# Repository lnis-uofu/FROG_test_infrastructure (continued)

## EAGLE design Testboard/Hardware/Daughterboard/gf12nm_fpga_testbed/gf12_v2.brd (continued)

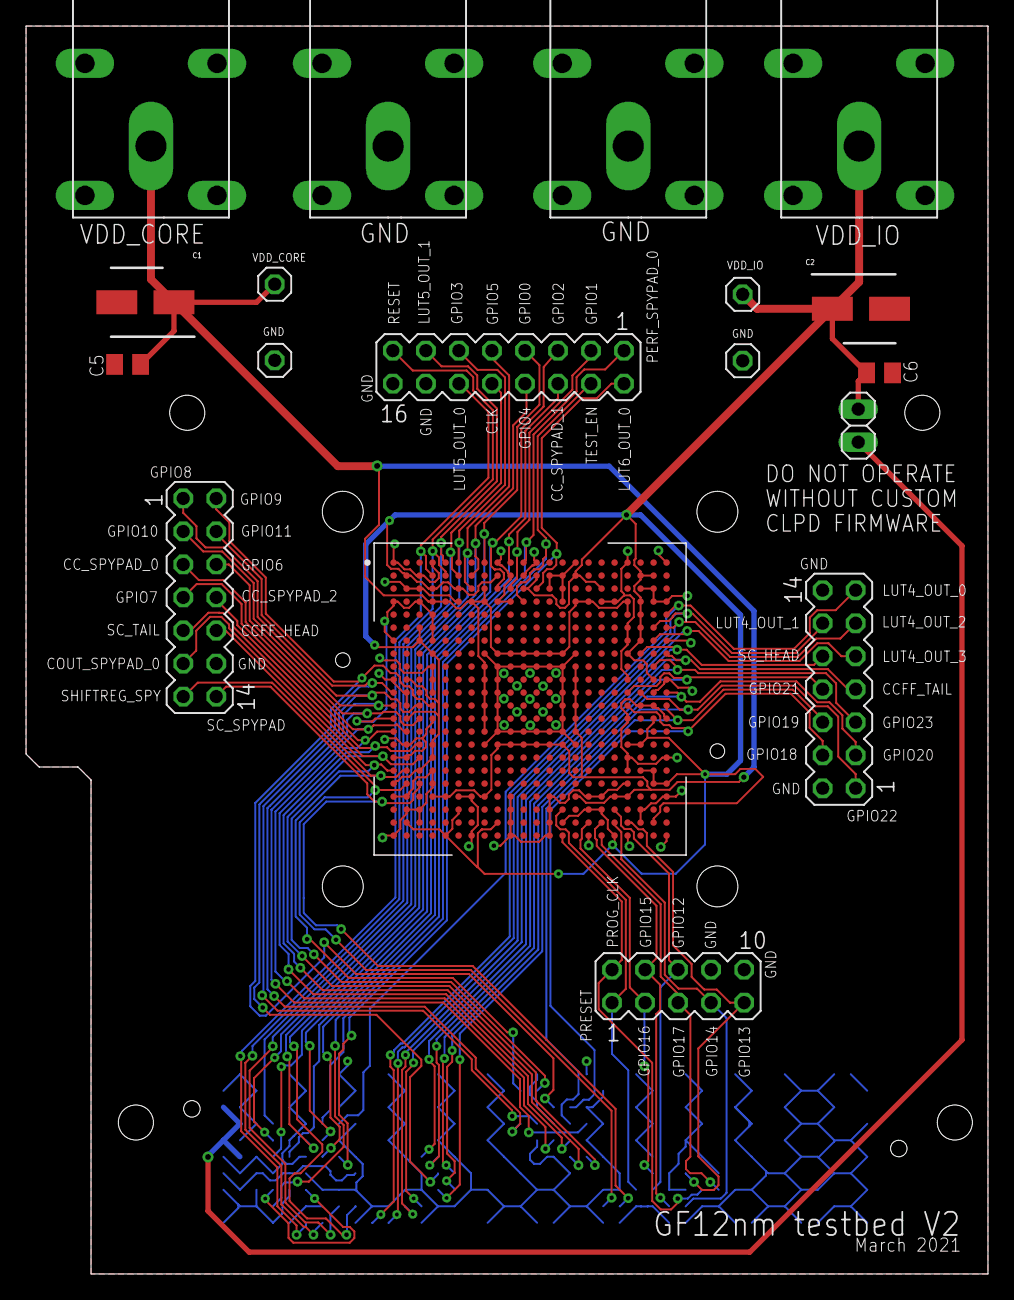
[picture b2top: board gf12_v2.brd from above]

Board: 2 copper layers, 74.0 x 96.0 mm, 19 parts (1 on the bottom side), 53 nets.

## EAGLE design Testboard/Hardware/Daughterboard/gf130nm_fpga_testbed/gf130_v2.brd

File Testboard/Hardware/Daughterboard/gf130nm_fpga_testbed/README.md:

# GF130nm PCB

## Pin Mappings

See [document](https://docs.google.com/spreadsheets/d/15zEyKyOejEvzYt_Ux2T2hlFm4bC0GtFkg6ObzwhrCUI) for pin mappings

## Changelog

### V2.2 Changes

**Critical Changes**
- Moved all pins connected to MPSoC MGT (bank 224) to other banks
- Moved all pins connected to lower-number TEBF0808 baord J1 pins to other banks
- Moved standoff mounting holes, were not lined up with TEBF0808 standoff holes

**Noncritical Changes**
- Extra FMC pins connected to more 2.54mm headers for MPSoC testbench GPIO
- Larger silkscreen text for 2.54mm headers

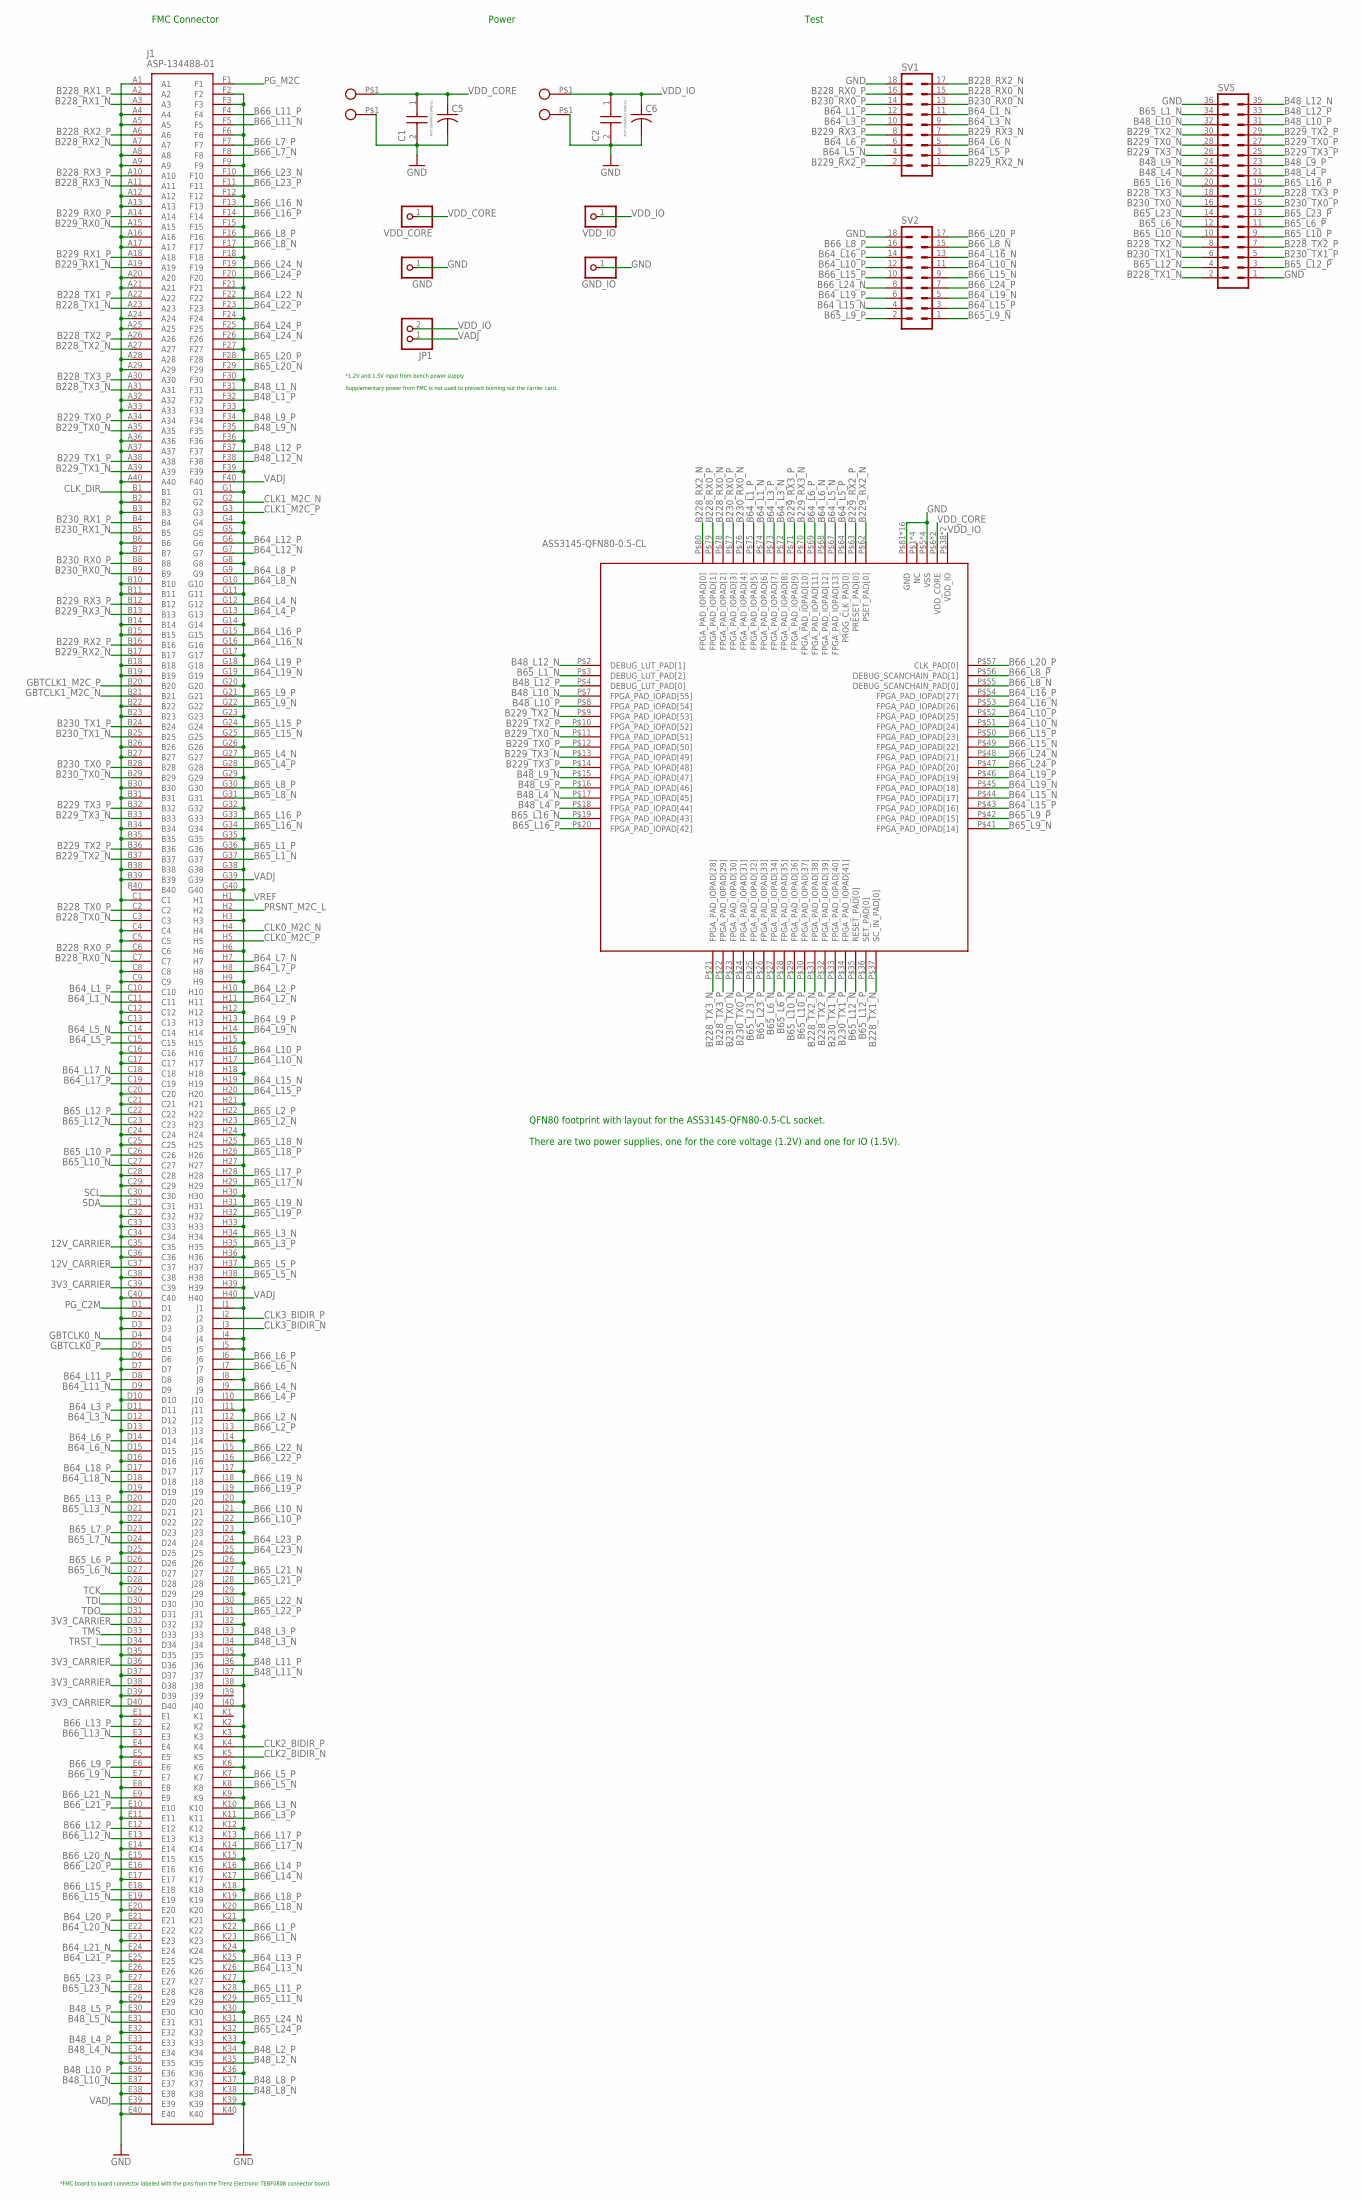
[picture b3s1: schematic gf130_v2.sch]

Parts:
C1, C2: APXT160ARA101ME61G; CAPAE530X610N
C5, C6: C-USC0805K; C0805K
GND: PINHD-1X1; 1X01
GND_IO: PINHD-1X1; 1X01
J1: ASP-134488-01; ASP13448801
JP1: PINHD-1X2; 1X02
SV1, SV2: MA09-2
SV5: MA18-2
U$2: QFN80; GF130
U$3, U$4, U$5: BANANA_JACK; 73099
VDD: BANANA_JACK; 73099
VDD_CORE: PINHD-1X1; 1X01
VDD_IO: PINHD-1X1; 1X01

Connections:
3V3_CARRIER: J1.C39, J1.D32, J1.D36, J1.D38, J1.D40
12V_CARRIER: J1.C35, J1.C37
B48_L1_N: J1.F31
B48_L1_P: J1.F32
B48_L2_N: J1.K35
B48_L2_P: J1.K34
B48_L3_N: J1.J34
B48_L3_P: J1.J33
B48_L4_N: J1.E34, SV5.22, U$2.P$17 (FPGA_PAD_IOPAD[45])
B48_L4_P: J1.E33, SV5.21, U$2.P$18 (FPGA_PAD_IOPAD[44])
B48_L5_N: J1.E31
B48_L5_P: J1.E30
B48_L8_N: J1.K38
B48_L8_P: J1.K37
B48_L9_N: J1.F35, SV5.24, U$2.P$15 (FPGA_PAD_IOPAD[47])
B48_L9_P: J1.F34, SV5.23, U$2.P$16 (FPGA_PAD_IOPAD[46])
B48_L10_N: J1.E37, SV5.32, U$2.P$7 (FPGA_PAD_IOPAD[55])
B48_L10_P: J1.E36, SV5.31, U$2.P$8 (FPGA_PAD_IOPAD[54])
B48_L11_N: J1.J37
B48_L11_P: J1.J36
B48_L12_N: J1.F38, SV5.35, U$2.P$2 (DEBUG_LUT_PAD[1])
B48_L12_P: J1.F37, SV5.33, U$2.P$4 (DEBUG_LUT_PAD[0])
B64_L1_N: J1.C11, SV1.11, U$2.P$74 (FPGA_PAD_IOPAD[6])
B64_L1_P: J1.C10, SV1.12, U$2.P$75 (FPGA_PAD_IOPAD[5])
B64_L2_N: J1.H11
B64_L2_P: J1.H10
B64_L3_N: J1.D12, SV1.9, U$2.P$72 (FPGA_PAD_IOPAD[8])
B64_L3_P: J1.D11, SV1.10, U$2.P$73 (FPGA_PAD_IOPAD[7])
B64_L4_N: J1.G12
B64_L4_P: J1.G13
B64_L5_N: J1.C14, SV1.4, U$2.P$67 (FPGA_PAD_IOPAD[13])
B64_L5_P: J1.C15, SV1.3, U$2.P$64 (PROG_CLK_PAD[0])
B64_L6_N: J1.D15, SV1.5, U$2.P$68 (FPGA_PAD_IOPAD[12])
B64_L6_P: J1.D14, SV1.6, U$2.P$69 (FPGA_PAD_IOPAD[11])
B64_L7_N: J1.H7
B64_L7_P: J1.H8
B64_L8_N: J1.G10
B64_L8_P: J1.G9
B64_L9_N: J1.H14
B64_L9_P: J1.H13
B64_L10_N: J1.H17, SV2.11, U$2.P$51 (FPGA_PAD_IOPAD[24])
B64_L10_P: J1.H16, SV2.12, U$2.P$52 (FPGA_PAD_IOPAD[25])
B64_L11_N: J1.D9
B64_L11_P: J1.D8
B64_L12_N: J1.G7
B64_L12_P: J1.G6
B64_L13_N: J1.K26
B64_L13_P: J1.K25
B64_L15_N: J1.H19, SV2.4, U$2.P$44 (FPGA_PAD_IOPAD[17])
B64_L15_P: J1.H20, SV2.3, U$2.P$43 (FPGA_PAD_IOPAD[16])
B64_L16_N: J1.G16, SV2.13, U$2.P$53 (FPGA_PAD_IOPAD[26])
B64_L16_P: J1.G15, SV2.14, U$2.P$54 (FPGA_PAD_IOPAD[27])
B64_L17_N: J1.C18
B64_L17_P: J1.C19
B64_L18_N: J1.D18
B64_L18_P: J1.D17
B64_L19_N: J1.G19, SV2.5, U$2.P$45 (FPGA_PAD_IOPAD[18])
B64_L19_P: J1.G18, SV2.6, U$2.P$46 (FPGA_PAD_IOPAD[19])
B64_L20_N: J1.E22
B64_L20_P: J1.E21
B64_L21_N: J1.E24
B64_L21_P: J1.E25
B64_L22_N: J1.F22
B64_L22_P: J1.F23
B64_L23_N: J1.J25
B64_L23_P: J1.J24
B64_L24_N: J1.F26
B64_L24_P: J1.F25
B65_L1_N: J1.G37, SV5.34, U$2.P$3 (DEBUG_LUT_PAD[2])
B65_L1_P: J1.G36
B65_L2_N: J1.H23
B65_L2_P: J1.H22
B65_L3_N: J1.H34
B65_L3_P: J1.H35
B65_L4_N: J1.G27
B65_L4_P: J1.G28
B65_L5_N: J1.H38
B65_L5_P: J1.H37
B65_L6_N: J1.D27, SV5.12, U$2.P$27 (FPGA_PAD_IOPAD[34])
B65_L6_P: J1.D26, SV5.11, U$2.P$28 (FPGA_PAD_IOPAD[35])
B65_L7_N: J1.D24
B65_L7_P: J1.D23
B65_L8_N: J1.G31
B65_L8_P: J1.G30
B65_L9_N: J1.G22, SV2.1, U$2.P$41 (FPGA_PAD_IOPAD[14])
B65_L9_P: J1.G21, SV2.2, U$2.P$42 (FPGA_PAD_IOPAD[15])
B65_L10_N: J1.C27, SV5.10, U$2.P$29 (FPGA_PAD_IOPAD[36])
B65_L10_P: J1.C26, SV5.9, U$2.P$30 (FPGA_PAD_IOPAD[37])
B65_L11_N: J1.K29
B65_L11_P: J1.K28
B65_L12_N: J1.C23, SV5.4, U$2.P$35 (RESET_PAD[0])
B65_L12_P: J1.C22, SV5.3, U$2.P$36 (SET_PAD[0])
B65_L13_N: J1.D21
B65_L13_P: J1.D20
B65_L15_N: J1.G25
B65_L15_P: J1.G24
B65_L16_N: J1.G34, SV5.20, U$2.P$19 (FPGA_PAD_IOPAD[43])
B65_L16_P: J1.G33, SV5.19, U$2.P$20 (FPGA_PAD_IOPAD[42])
B65_L17_N: J1.H29
B65_L17_P: J1.H28
B65_L18_N: J1.H25
B65_L18_P: J1.H26
B65_L19_N: J1.H31
B65_L19_P: J1.H32
B65_L20_N: J1.F29
B65_L20_P: J1.F28
B65_L21_N: J1.J27
B65_L21_P: J1.J28
B65_L22_N: J1.J30
B65_L22_P: J1.J31
B65_L23_N: J1.E28, SV5.14, U$2.P$25 (FPGA_PAD_IOPAD[32])
B65_L23_P: J1.E27, SV5.13, U$2.P$26 (FPGA_PAD_IOPAD[33])
B65_L24_N: J1.K31
B65_L24_P: J1.K32
B66_L1_N: J1.K23
B66_L1_P: J1.K22
B66_L2_N: J1.J12
B66_L2_P: J1.J13
B66_L3_N: J1.K10
B66_L3_P: J1.K11
B66_L4_N: J1.J9
B66_L4_P: J1.J10
B66_L5_N: J1.K8
B66_L5_P: J1.K7
B66_L6_N: J1.J7
B66_L6_P: J1.J6
B66_L7_N: J1.F8
B66_L7_P: J1.F7
B66_L8_N: J1.F17, SV2.15, U$2.P$55 (DEBUG_SCANCHAIN_PAD[0])
B66_L8_P: J1.F16, SV2.16, U$2.P$56 (DEBUG_SCANCHAIN_PAD[1])
B66_L9_N: J1.E7
B66_L9_P: J1.E6
B66_L10_N: J1.J21
B66_L10_P: J1.J22
B66_L11_N: J1.F5
B66_L11_P: J1.F4
B66_L12_N: J1.E13
B66_L12_P: J1.E12
B66_L13_N: J1.E3
B66_L13_P: J1.E2
B66_L14_N: J1.K17
B66_L14_P: J1.K16
B66_L15_N: J1.E19, SV2.9, U$2.P$49 (FPGA_PAD_IOPAD[22])
B66_L15_P: J1.E18, SV2.10, U$2.P$50 (FPGA_PAD_IOPAD[23])
B66_L16_N: J1.F13
B66_L16_P: J1.F14
B66_L17_N: J1.K14
B66_L17_P: J1.K13
B66_L18_N: J1.K20
B66_L18_P: J1.K19
B66_L19_N: J1.J18
B66_L19_P: J1.J19
B66_L20_N: J1.E15
B66_L20_P: J1.E16, SV2.17, U$2.P$57 (CLK_PAD[0])
B66_L21_N: J1.E9
B66_L21_P: J1.E10
B66_L22_N: J1.J15
B66_L22_P: J1.J16
B66_L23_N: J1.F10
B66_L23_P: J1.F11
B66_L24_N: J1.F19, SV2.8, U$2.P$48 (FPGA_PAD_IOPAD[21])
B66_L24_P: J1.F20, SV2.7, U$2.P$47 (FPGA_PAD_IOPAD[20])
B228_RX0_N: J1.C7, SV1.15, U$2.P$78 (FPGA_PAD_IOPAD[2])
B228_RX0_P: J1.C6, SV1.16, U$2.P$79 (FPGA_PAD_IOPAD[1])
B228_RX1_N: J1.A3
B228_RX1_P: J1.A2
B228_RX2_N: J1.A7, SV1.17, U$2.P$80 (FPGA_PAD_IOPAD[0])
B228_RX2_P: J1.A6
B228_RX3_N: J1.A11
B228_RX3_P: J1.A10
B228_TX0_N: J1.C3
B228_TX0_P: J1.C2
B228_TX1_N: J1.A23, SV5.2, U$2.P$37 (SC_IN_PAD[0])
B228_TX1_P: J1.A22
B228_TX2_N: J1.A27, SV5.8, U$2.P$31 (FPGA_PAD_IOPAD[38])
B228_TX2_P: J1.A26, SV5.7, U$2.P$32 (FPGA_PAD_IOPAD[39])
B228_TX3_N: J1.A31, SV5.18, U$2.P$21 (FPGA_PAD_IOPAD[28])
B228_TX3_P: J1.A30, SV5.17, U$2.P$22 (FPGA_PAD_IOPAD[29])
B229_RX0_N: J1.A15
B229_RX0_P: J1.A14
B229_RX1_N: J1.A19
B229_RX1_P: J1.A18
B229_RX2_N: J1.B17, SV1.1, U$2.P$62 (PSET_PAD[0])
B229_RX2_P: J1.B16, SV1.2, U$2.P$63 (PRESET_PAD[0])
B229_RX3_N: J1.B13, SV1.7, U$2.P$70 (FPGA_PAD_IOPAD[10])
B229_RX3_P: J1.B12, SV1.8, U$2.P$71 (FPGA_PAD_IOPAD[9])
B229_TX0_N: J1.A35, SV5.28, U$2.P$11 (FPGA_PAD_IOPAD[51])
B229_TX0_P: J1.A34, SV5.27, U$2.P$12 (FPGA_PAD_IOPAD[50])
B229_TX1_N: J1.A39
B229_TX1_P: J1.A38
B229_TX2_N: J1.B37, SV5.30, U$2.P$9 (FPGA_PAD_IOPAD[53])
B229_TX2_P: J1.B36, SV5.29, U$2.P$10 (FPGA_PAD_IOPAD[52])
B229_TX3_N: J1.B33, SV5.26, U$2.P$13 (FPGA_PAD_IOPAD[49])
B229_TX3_P: J1.B32, SV5.25, U$2.P$14 (FPGA_PAD_IOPAD[48])
B230_RX0_N: J1.B9, SV1.13, U$2.P$76 (FPGA_PAD_IOPAD[4])
B230_RX0_P: J1.B8, SV1.14, U$2.P$77 (FPGA_PAD_IOPAD[3])
B230_RX1_N: J1.B5
B230_RX1_P: J1.B4
B230_TX0_N: J1.B29, SV5.16, U$2.P$23 (FPGA_PAD_IOPAD[30])
B230_TX0_P: J1.B28, SV5.15, U$2.P$24 (FPGA_PAD_IOPAD[31])
B230_TX1_N: J1.B25, SV5.6, U$2.P$33 (FPGA_PAD_IOPAD[40])
B230_TX1_P: J1.B24, SV5.5, U$2.P$34 (FPGA_PAD_IOPAD[41])
CLK0_M2C_N: J1.H4
CLK0_M2C_P: J1.H5
CLK1_M2C_N: J1.G2
CLK1_M2C_P: J1.G3
CLK2_BIDIR_N: J1.K5
CLK2_BIDIR_P: J1.K4
CLK3_BIDIR_N: J1.J3
CLK3_BIDIR_P: J1.J2
CLK_DIR: J1.B1
GBTCLK0_N: J1.D4
GBTCLK0_P: J1.D5
GBTCLK1_M2C_N: J1.B21
GBTCLK1_M2C_P: J1.B20
GND: C1.2 (-), C2.2 (-), C5.2, C6.2, GND.1, GND_IO.1, J1.A1, J1.A4, J1.A5, J1.A8, J1.A9, J1.A12, J1.A13, J1.A16, J1.A17, J1.A20, J1.A21, J1.A24, J1.A25, J1.A28, J1.A29, J1.A32, J1.A33, J1.A36, J1.A37, J1.A40, J1.B2, J1.B3, J1.B6, J1.B7, J1.B10, J1.B11, J1.B14, J1.B15, J1.B18, J1.B19, J1.B22, J1.B23, J1.B26, J1.B27, J1.B30, J1.B31, J1.B34, J1.B35, J1.B38, J1.B39, J1.C1, J1.C4, J1.C5, J1.C8, J1.C9, J1.C12, J1.C13, J1.C16, J1.C17, J1.C20, J1.C21, J1.C24, J1.C25, J1.C28, J1.C29, J1.C32, J1.C33, J1.C34, J1.C36, J1.C38, J1.C40, J1.D2, J1.D3, J1.D6, J1.D7, J1.D10, J1.D13, J1.D16, J1.D19, J1.D22, J1.D25, J1.D28, J1.D35, J1.D37, J1.D39, J1.E1, J1.E4, J1.E5, J1.E8, J1.E11, J1.E14, J1.E17, J1.E20, J1.E23, J1.E26, J1.E29, J1.E32, J1.E35, J1.E38, J1.E40, J1.F2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
PG_C2M: J1.D1
PG_M2C: J1.F1
PRSNT_M2C_L: J1.H2
SCL: J1.C30
SDA: J1.C31
TCK: J1.D29
TDI: J1.D30
TDO: J1.D31
TMS: J1.D33
TRST_L: J1.D34
VADJ: J1.E39, J1.F40, J1.G39, J1.H40, JP1.1
VDD_CORE: C1.1 (+), C5.1, U$2.P$6 (VDD_CORE), U$2.P$58 (VDD_CORE), VDD.P$1 (1), VDD_CORE.1
VDD_IO: C2.1 (+), C6.1, JP1.2, U$2.P$38 (VDD_IO), U$2.P$66 (VDD_IO), U$4.P$1 (1), VDD_IO.1
VREF: J1.H1

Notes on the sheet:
Power
FMC Connector
*1.2V and 1.5V input from bench power supply Supplementary power from FMC is not used to prevent burning out the carrier card.
*FMC board to board connector labeled with the pins from the Trenz Electronic TEBF0808 connector board.
QFN80 footprint with layout for the ASS3145-QFN80-0.5-CL socket. There are two power supplies, one for the core voltage (1.2V) and one for IO (1.5V).
Test

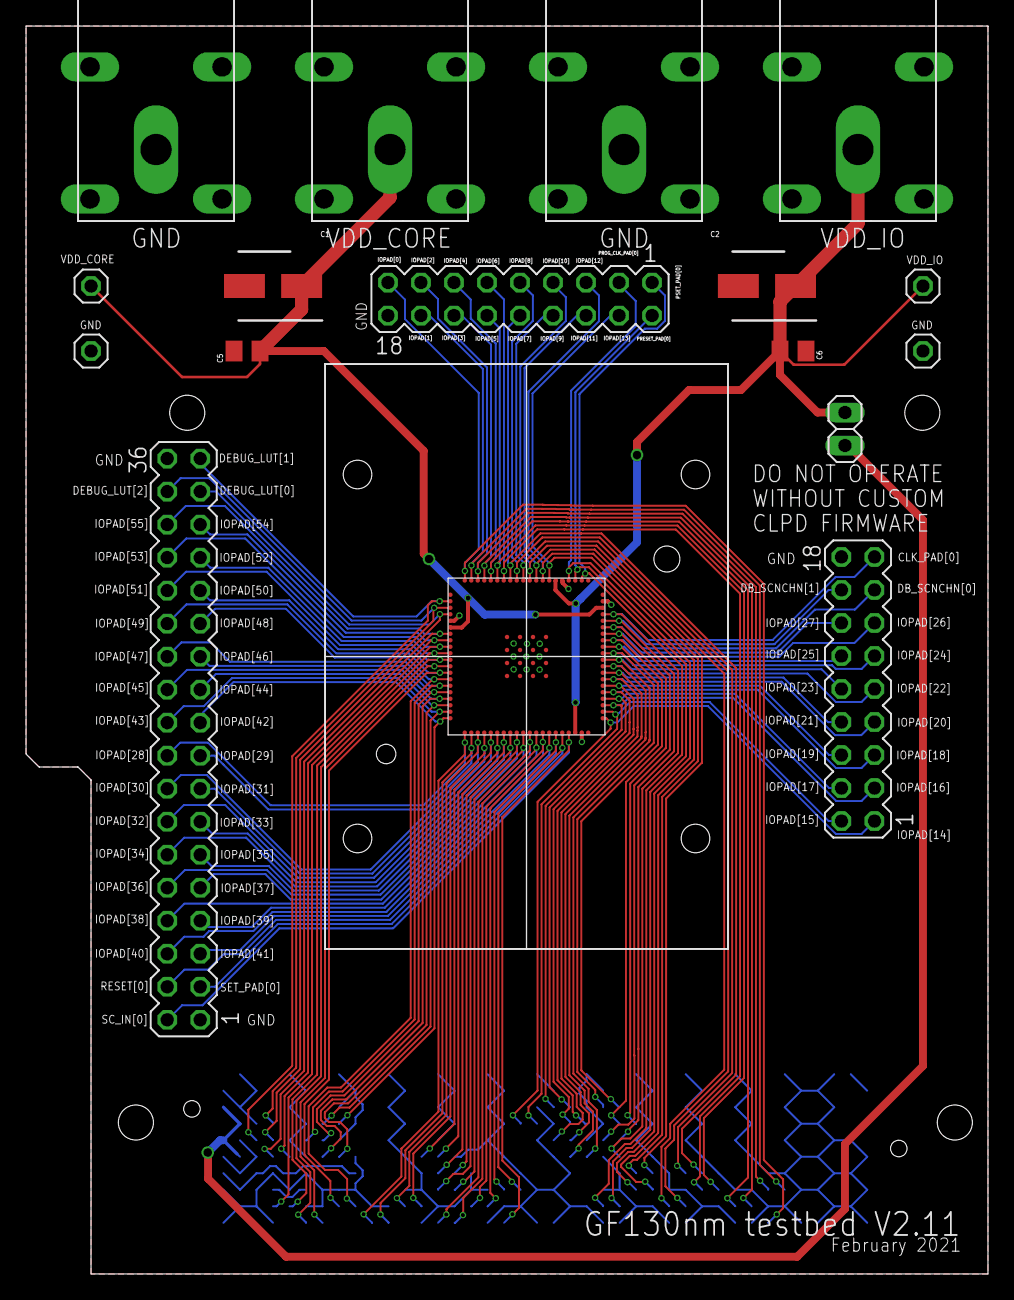
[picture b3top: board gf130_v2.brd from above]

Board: 2 copper layers, 74.0 x 96.0 mm, 18 parts (1 on the bottom side), 74 nets.

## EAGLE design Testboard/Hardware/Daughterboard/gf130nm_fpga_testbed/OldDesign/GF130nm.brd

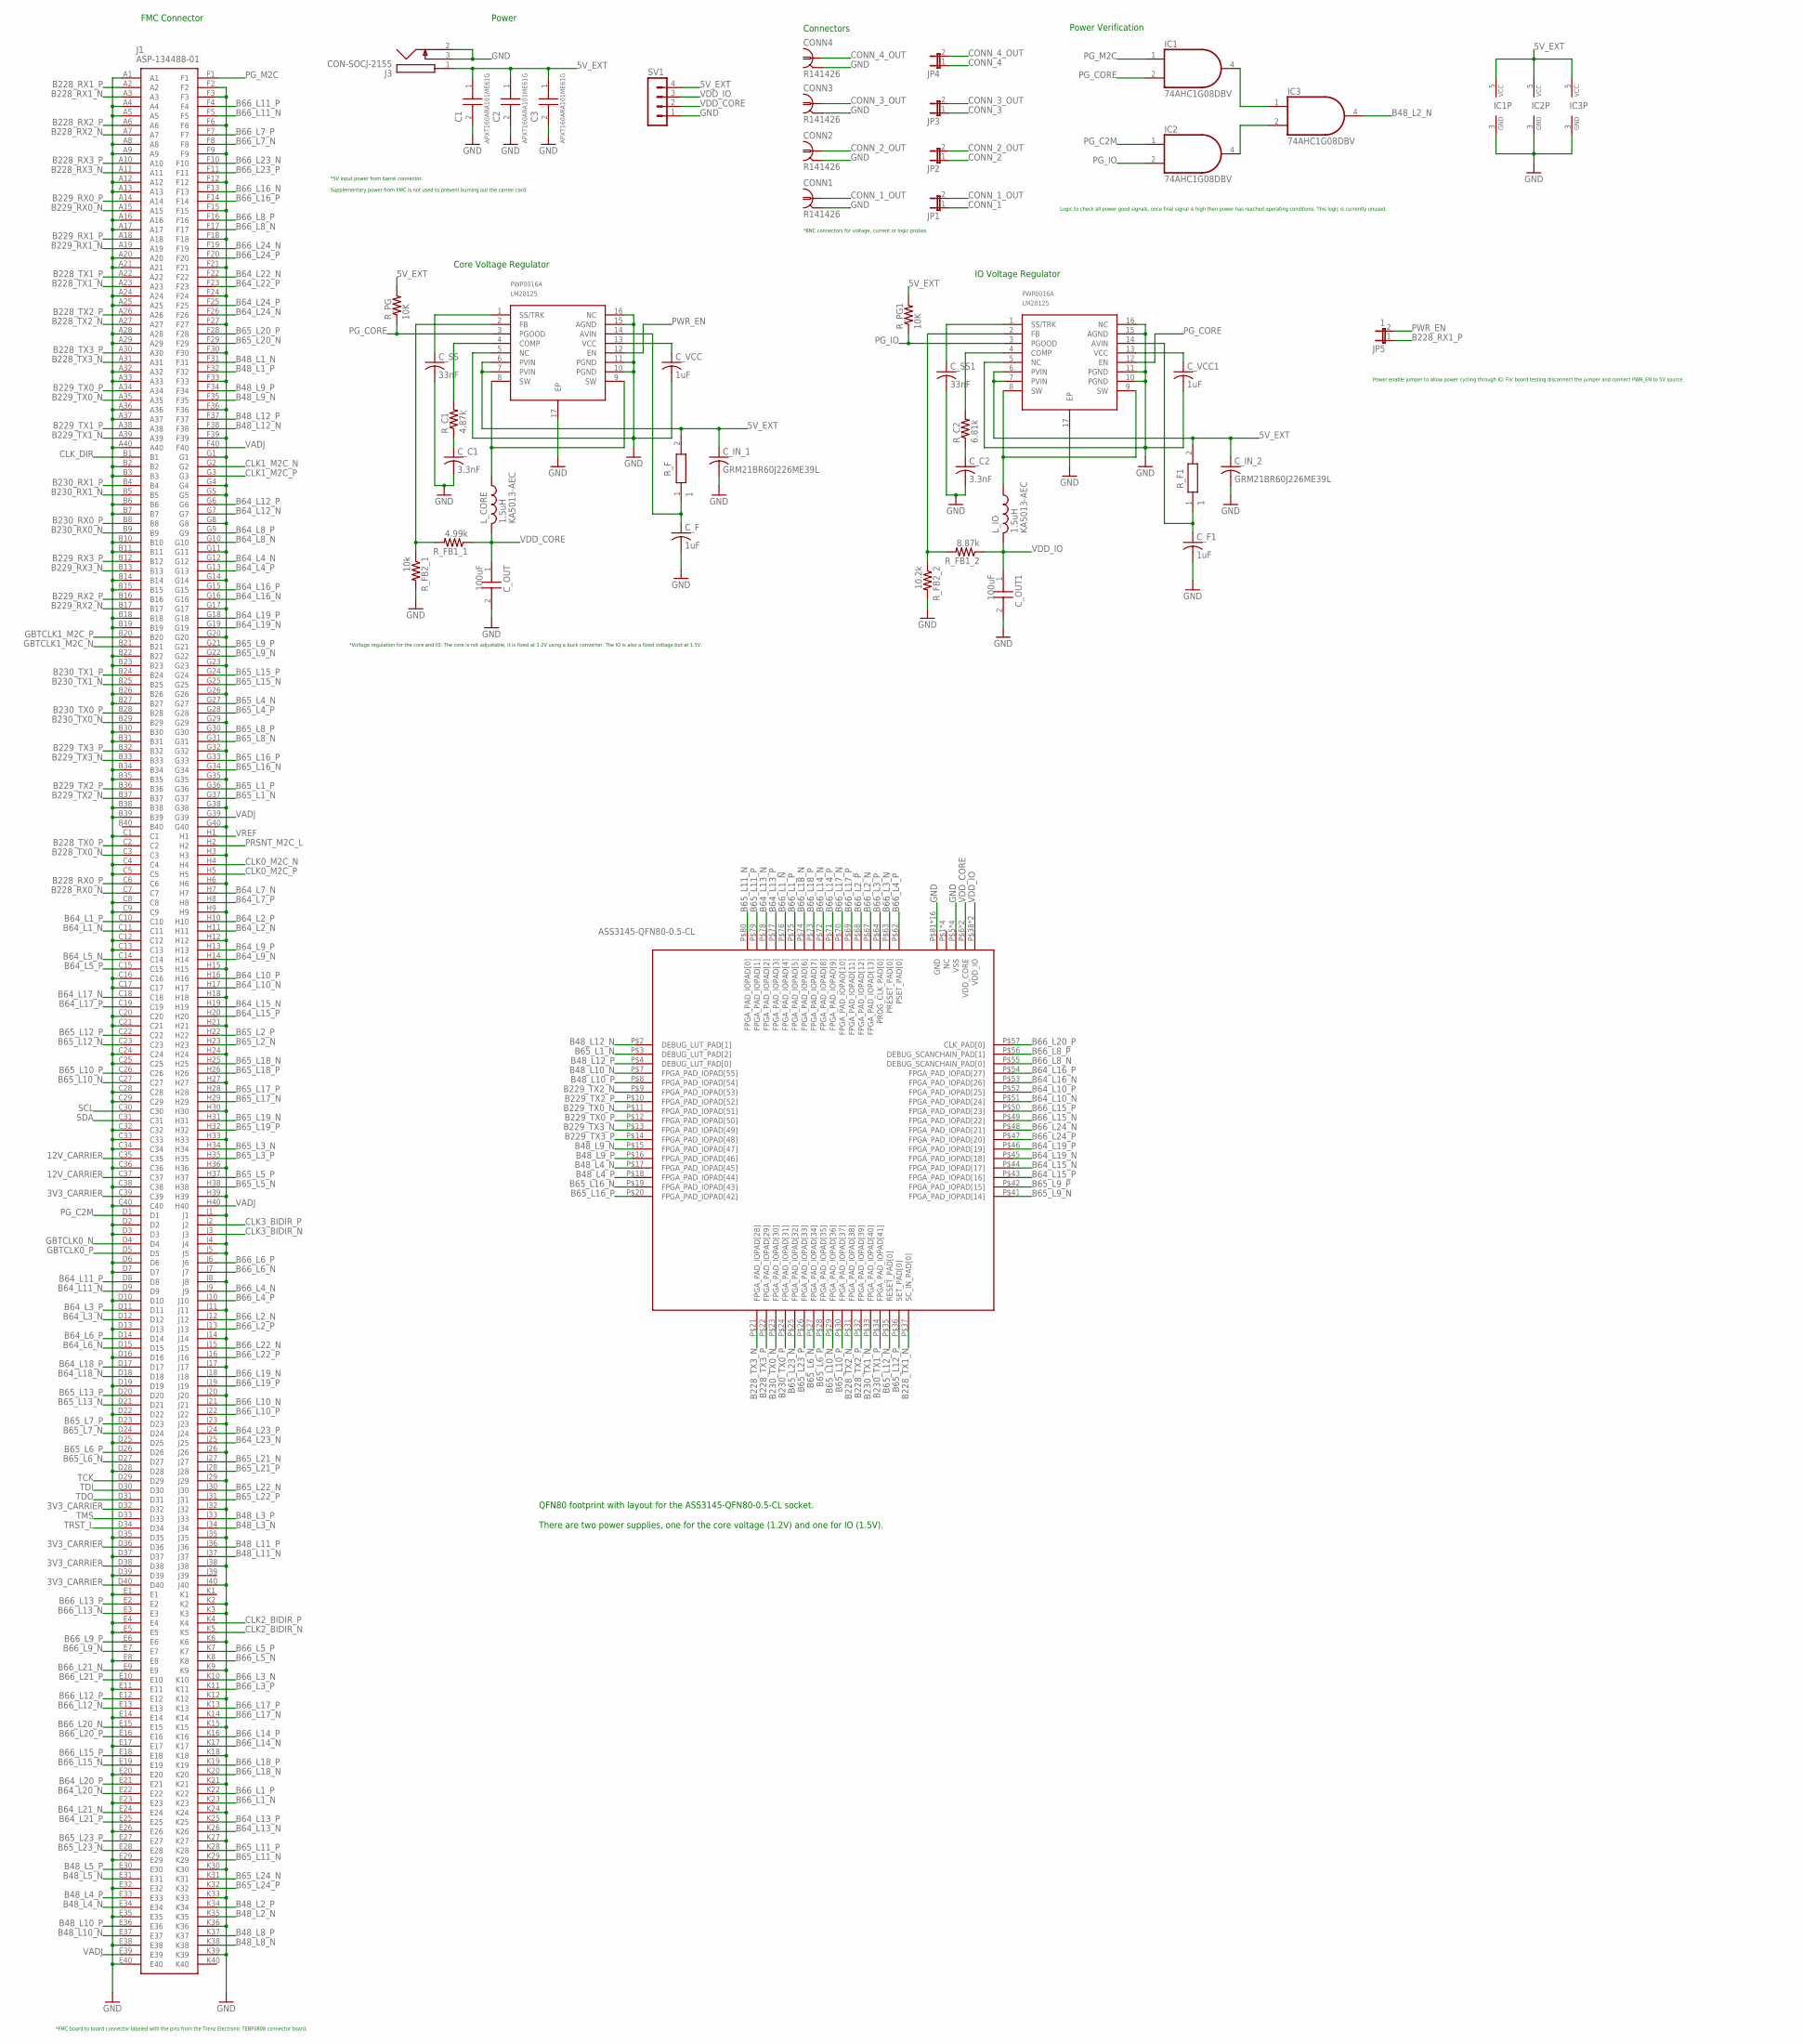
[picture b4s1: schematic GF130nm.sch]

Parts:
C1, C2, C3: APXT160ARA101ME61G; CAPAE530X610N
CONN1, CONN2, CONN3, CONN4: R141426
C_C1, C_C2: 3.3nF; C0805
C_F, C_F1: 1uF; C0805
C_IN_1, C_IN_2: GRM21BR60J226ME39L; CAPC2012X125N
C_OUT, C_OUT1: 100uF; CAPC2012X145N
C_SS, C_SS1: 33nF; C0805
C_VCC, C_VCC1: 1uF; C0805
IC1, IC2, IC3: 74AHC1G08DBV; SOT23-5
J1: ASP-134488-01; ASP13448801
J3: CON-SOCJ-2155; CONSOCJ2155
JP1, JP2, JP3, JP4: JP1E; JP1
JP5: 1; JP1
L_CORE: KA5013-AEC; INDDFN400X400X180-2N
L_IO: KA5013-AEC; INDDFN400X400X180-2N
R_C1: 4.87k; R0805
R_C2: 6.81k; R0805
R_F, R_F1: 1; RESC1608X55N
R_FB1_1: 4.99k; R0805
R_FB1_2: 8.87k; R0805
R_FB2_1: 10k; R0805
R_FB2_2: 10.2k; R0805
R_PG, R_PG1: 10K; R0805
SV1: MA04-1
U$2: QFN80; GF130
VDD_CORE: LM20125/LM20125Q; SOP65P640X120-17T330L
VDD_IO: LM20125/LM20125Q; SOP65P640X120-17T330L

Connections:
3V3_CARRIER: J1.C39, J1.D32, J1.D36, J1.D38, J1.D40
5V_EXT: C1.1 (+), C2.1 (+), C3.1 (+), C_IN_1.1, C_IN_2.1, IC1.5 (VCC), IC2.5 (VCC), IC3.5 (VCC), J3.1, R_F.2, R_F1.2, R_PG.2, R_PG1.2, SV1.4, VDD_CORE.6 (PVIN), VDD_CORE.7 (PVIN), VDD_IO.6 (PVIN), VDD_IO.7 (PVIN)
12V_CARRIER: J1.C35, J1.C37
B48_L1_N: J1.F31
B48_L1_P: J1.F32
B48_L2_N: IC3.4 (O), J1.K35
B48_L2_P: J1.K34
B48_L3_N: J1.J34
B48_L3_P: J1.J33
B48_L4_N: J1.E34, U$2.P$17 (FPGA_PAD_IOPAD[45])
B48_L4_P: J1.E33, U$2.P$18 (FPGA_PAD_IOPAD[44])
B48_L5_N: J1.E31
B48_L5_P: J1.E30
B48_L8_N: J1.K38
B48_L8_P: J1.K37
B48_L9_N: J1.F35, U$2.P$15 (FPGA_PAD_IOPAD[47])
B48_L9_P: J1.F34, U$2.P$16 (FPGA_PAD_IOPAD[46])
B48_L10_N: J1.E37, U$2.P$7 (FPGA_PAD_IOPAD[55])
B48_L10_P: J1.E36, U$2.P$8 (FPGA_PAD_IOPAD[54])
B48_L11_N: J1.J37
B48_L11_P: J1.J36
B48_L12_N: J1.F38, U$2.P$2 (DEBUG_LUT_PAD[1])
B48_L12_P: J1.F37, U$2.P$4 (DEBUG_LUT_PAD[0])
B64_L1_N: J1.C11
B64_L1_P: J1.C10
B64_L2_N: J1.H11
B64_L2_P: J1.H10
B64_L3_N: J1.D12
B64_L3_P: J1.D11
B64_L4_N: J1.G12
B64_L4_P: J1.G13
B64_L5_N: J1.C14
B64_L5_P: J1.C15
B64_L6_N: J1.D15
B64_L6_P: J1.D14
B64_L7_N: J1.H7
B64_L7_P: J1.H8
B64_L8_N: J1.G10
B64_L8_P: J1.G9
B64_L9_N: J1.H14
B64_L9_P: J1.H13
B64_L10_N: J1.H17, U$2.P$51 (FPGA_PAD_IOPAD[24])
B64_L10_P: J1.H16, U$2.P$52 (FPGA_PAD_IOPAD[25])
B64_L11_N: J1.D9
B64_L11_P: J1.D8
B64_L12_N: J1.G7
B64_L12_P: J1.G6
B64_L13_N: J1.K26, U$2.P$78 (FPGA_PAD_IOPAD[2])
B64_L13_P: J1.K25, U$2.P$77 (FPGA_PAD_IOPAD[3])
B64_L15_N: J1.H19, U$2.P$44 (FPGA_PAD_IOPAD[17])
B64_L15_P: J1.H20, U$2.P$43 (FPGA_PAD_IOPAD[16])
B64_L16_N: J1.G16, U$2.P$53 (FPGA_PAD_IOPAD[26])
B64_L16_P: J1.G15, U$2.P$54 (FPGA_PAD_IOPAD[27])
B64_L17_N: J1.C18
B64_L17_P: J1.C19
B64_L18_N: J1.D18
B64_L18_P: J1.D17
B64_L19_N: J1.G19, U$2.P$45 (FPGA_PAD_IOPAD[18])
B64_L19_P: J1.G18, U$2.P$46 (FPGA_PAD_IOPAD[19])
B64_L20_N: J1.E22
B64_L20_P: J1.E21
B64_L21_N: J1.E24
B64_L21_P: J1.E25
B64_L22_N: J1.F22
B64_L22_P: J1.F23
B64_L23_N: J1.J25
B64_L23_P: J1.J24
B64_L24_N: J1.F26
B64_L24_P: J1.F25
B65_L1_N: J1.G37, U$2.P$3 (DEBUG_LUT_PAD[2])
B65_L1_P: J1.G36
B65_L2_N: J1.H23
B65_L2_P: J1.H22
B65_L3_N: J1.H34
B65_L3_P: J1.H35
B65_L4_N: J1.G27
B65_L4_P: J1.G28
B65_L5_N: J1.H38
B65_L5_P: J1.H37
B65_L6_N: J1.D27, U$2.P$27 (FPGA_PAD_IOPAD[34])
B65_L6_P: J1.D26, U$2.P$28 (FPGA_PAD_IOPAD[35])
B65_L7_N: J1.D24
B65_L7_P: J1.D23
B65_L8_N: J1.G31
B65_L8_P: J1.G30
B65_L9_N: J1.G22, U$2.P$41 (FPGA_PAD_IOPAD[14])
B65_L9_P: J1.G21, U$2.P$42 (FPGA_PAD_IOPAD[15])
B65_L10_N: J1.C27, U$2.P$29 (FPGA_PAD_IOPAD[36])
B65_L10_P: J1.C26, U$2.P$30 (FPGA_PAD_IOPAD[37])
B65_L11_N: J1.K29, U$2.P$80 (FPGA_PAD_IOPAD[0])
B65_L11_P: J1.K28, U$2.P$79 (FPGA_PAD_IOPAD[1])
B65_L12_N: J1.C23, U$2.P$35 (RESET_PAD[0])
B65_L12_P: J1.C22, U$2.P$36 (SET_PAD[0])
B65_L13_N: J1.D21
B65_L13_P: J1.D20
B65_L15_N: J1.G25
B65_L15_P: J1.G24
B65_L16_N: J1.G34, U$2.P$19 (FPGA_PAD_IOPAD[43])
B65_L16_P: J1.G33, U$2.P$20 (FPGA_PAD_IOPAD[42])
B65_L17_N: J1.H29
B65_L17_P: J1.H28
B65_L18_N: J1.H25
B65_L18_P: J1.H26
B65_L19_N: J1.H31
B65_L19_P: J1.H32
B65_L20_N: J1.F29
B65_L20_P: J1.F28
B65_L21_N: J1.J27
B65_L21_P: J1.J28
B65_L22_N: J1.J30
B65_L22_P: J1.J31
B65_L23_N: J1.E28, U$2.P$25 (FPGA_PAD_IOPAD[32])
B65_L23_P: J1.E27, U$2.P$26 (FPGA_PAD_IOPAD[33])
B65_L24_N: J1.K31
B65_L24_P: J1.K32
B66_L1_N: J1.K23, U$2.P$76 (FPGA_PAD_IOPAD[4])
B66_L1_P: J1.K22, U$2.P$75 (FPGA_PAD_IOPAD[5])
B66_L2_N: J1.J12, U$2.P$67 (FPGA_PAD_IOPAD[13])
B66_L2_P: J1.J13, U$2.P$68 (FPGA_PAD_IOPAD[12])
B66_L3_N: J1.K10, U$2.P$63 (PRESET_PAD[0])
B66_L3_P: J1.K11, U$2.P$64 (PROG_CLK_PAD[0])
B66_L4_N: J1.J9
B66_L4_P: J1.J10, U$2.P$62 (PSET_PAD[0])
B66_L5_N: J1.K8
B66_L5_P: J1.K7
B66_L6_N: J1.J7
B66_L6_P: J1.J6
B66_L7_N: J1.F8
B66_L7_P: J1.F7
B66_L8_N: J1.F17, U$2.P$55 (DEBUG_SCANCHAIN_PAD[0])
B66_L8_P: J1.F16, U$2.P$56 (DEBUG_SCANCHAIN_PAD[1])
B66_L9_N: J1.E7
B66_L9_P: J1.E6
B66_L10_N: J1.J21
B66_L10_P: J1.J22
B66_L11_N: J1.F5
B66_L11_P: J1.F4
B66_L12_N: J1.E13
B66_L12_P: J1.E12
B66_L13_N: J1.E3
B66_L13_P: J1.E2
B66_L14_N: J1.K17, U$2.P$72 (FPGA_PAD_IOPAD[8])
B66_L14_P: J1.K16, U$2.P$71 (FPGA_PAD_IOPAD[9])
B66_L15_N: J1.E19, U$2.P$49 (FPGA_PAD_IOPAD[22])
B66_L15_P: J1.E18, U$2.P$50 (FPGA_PAD_IOPAD[23])
B66_L16_N: J1.F13
B66_L16_P: J1.F14
B66_L17_N: J1.K14, U$2.P$70 (FPGA_PAD_IOPAD[10])
B66_L17_P: J1.K13, U$2.P$69 (FPGA_PAD_IOPAD[11])
B66_L18_N: J1.K20, U$2.P$74 (FPGA_PAD_IOPAD[6])
B66_L18_P: J1.K19, U$2.P$73 (FPGA_PAD_IOPAD[7])
B66_L19_N: J1.J18
B66_L19_P: J1.J19
B66_L20_N: J1.E15
B66_L20_P: J1.E16, U$2.P$57 (CLK_PAD[0])
B66_L21_N: J1.E9
B66_L21_P: J1.E10
B66_L22_N: J1.J15
B66_L22_P: J1.J16
B66_L23_N: J1.F10
B66_L23_P: J1.F11
B66_L24_N: J1.F19, U$2.P$48 (FPGA_PAD_IOPAD[21])
B66_L24_P: J1.F20, U$2.P$47 (FPGA_PAD_IOPAD[20])
B228_RX0_N: J1.C7
B228_RX0_P: J1.C6
B228_RX1_N: J1.A3
B228_RX1_P: J1.A2, JP5.1
B228_RX2_N: J1.A7
B228_RX2_P: J1.A6
B228_RX3_N: J1.A11
B228_RX3_P: J1.A10
B228_TX0_N: J1.C3
B228_TX0_P: J1.C2
B228_TX1_N: J1.A23, U$2.P$37 (SC_IN_PAD[0])
B228_TX1_P: J1.A22
B228_TX2_N: J1.A27, U$2.P$31 (FPGA_PAD_IOPAD[38])
B228_TX2_P: J1.A26, U$2.P$32 (FPGA_PAD_IOPAD[39])
B228_TX3_N: J1.A31, U$2.P$21 (FPGA_PAD_IOPAD[28])
B228_TX3_P: J1.A30, U$2.P$22 (FPGA_PAD_IOPAD[29])
B229_RX0_N: J1.A15
B229_RX0_P: J1.A14
B229_RX1_N: J1.A19
B229_RX1_P: J1.A18
B229_RX2_N: J1.B17
B229_RX2_P: J1.B16
B229_RX3_N: J1.B13
B229_RX3_P: J1.B12
B229_TX0_N: J1.A35, U$2.P$11 (FPGA_PAD_IOPAD[51])
B229_TX0_P: J1.A34, U$2.P$12 (FPGA_PAD_IOPAD[50])
B229_TX1_N: J1.A39
B229_TX1_P: J1.A38
B229_TX2_N: J1.B37, U$2.P$9 (FPGA_PAD_IOPAD[53])
B229_TX2_P: J1.B36, U$2.P$10 (FPGA_PAD_IOPAD[52])
B229_TX3_N: J1.B33, U$2.P$13 (FPGA_PAD_IOPAD[49])
B229_TX3_P: J1.B32, U$2.P$14 (FPGA_PAD_IOPAD[48])
B230_RX0_N: J1.B9
B230_RX0_P: J1.B8
B230_RX1_N: J1.B5
B230_RX1_P: J1.B4
B230_TX0_N: J1.B29, U$2.P$23 (FPGA_PAD_IOPAD[30])
B230_TX0_P: J1.B28, U$2.P$24 (FPGA_PAD_IOPAD[31])
B230_TX1_N: J1.B25, U$2.P$33 (FPGA_PAD_IOPAD[40])
B230_TX1_P: J1.B24, U$2.P$34 (FPGA_PAD_IOPAD[41])
CLK0_M2C_N: J1.H4
CLK0_M2C_P: J1.H5
CLK1_M2C_N: J1.G2
CLK1_M2C_P: J1.G3
CLK2_BIDIR_N: J1.K5
CLK2_BIDIR_P: J1.K4
CLK3_BIDIR_N: J1.J3
CLK3_BIDIR_P: J1.J2
CLK_DIR: J1.B1
CONN_1: JP1.1
CONN_1_OUT: CONN1.1, JP1.2
CONN_2: JP2.1
CONN_2_OUT: CONN2.1, JP2.2
CONN_3: JP3.1
CONN_3_OUT: CONN3.1, JP3.2
CONN_4: JP4.1
CONN_4_OUT: CONN4.1, JP4.2
FB: R_FB1_2.2, R_FB2_2.1, VDD_IO.2 (FB)
GBTCLK0_N: J1.D4
GBTCLK0_P: J1.D5
GBTCLK1_M2C_N: J1.B21
GBTCLK1_M2C_P: J1.B20
GND: C1.2 (-), C2.2 (-), C3.2 (-), CONN1.2, CONN1.3 (2), CONN1.4 (2), CONN1.5 (2), CONN2.2, CONN2.3 (2), CONN2.4 (2), CONN2.5 (2), CONN3.2, CONN3.3 (2), CONN3.4 (2), CONN3.5 (2), CONN4.2, CONN4.3 (2), CONN4.4 (2), CONN4.5 (2), C_C1.2, C_C2.2, C_F.2, C_F1.2, C_IN_1.2, C_IN_2.2, C_OUT.2, C_OUT1.2, C_SS.2, C_SS1.2, C_VCC.2, C_VCC1.2, IC1.3 (GND), IC2.3 (GND), IC3.3 (GND), J1.A1, J1.A4, J1.A5, J1.A8, J1.A9, J1.A12, J1.A13, J1.A16, J1.A17, J1.A20, J1.A21, J1.A24, J1.A25, J1.A28, J1.A29, J1.A32, J1.A33, J1.A36, J1.A37, J1.A40, J1.B2, J1.B3, J1.B6, J1.B7, J1.B10, J1.B11, J1.B14, J1.B15, J1.B18, J1.B19, J1.B22, J1.B23, J1.B26, J1.B27, J1.B30, J1.B31, J1.B34, J1.B35, J1.B38, J1.B39, J1.C1, J1.C4, J1.C5, J1.C8, J1.C9, J1.C12, J1.C13, J1.C16, J1.C17, J1.C20, J1.C21, J1.C24, J1.C25, J1.C28, J1.C29, J1.C32, J1.C33, J1.C34, J1.C36, J1.C38, J1.C40, J1.D2, J1.D3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
unnamed: R_C2.2, VDD_IO.4 (COMP)
unnamed: C_SS.1, VDD_CORE.1 (SS/TRK)
unnamed: R_C1.2, VDD_CORE.4 (COMP)
unnamed: C_C1.1, R_C1.1
unnamed: C_VCC.1, VDD_CORE.13 (VCC)
unnamed: C_C2.1, R_C2.1
unnamed: L_CORE.1, VDD_CORE.8 (SW), VDD_CORE.9 (SW)
unnamed: C_VCC1.1, VDD_IO.13 (VCC)
unnamed: C_SS1.1, VDD_IO.1 (SS/TRK)
unnamed: L_IO.1, VDD_IO.8 (SW), VDD_IO.9 (SW)
unnamed: C_F1.1, R_F1.1, VDD_IO.14 (AVIN)
unnamed: C_F.1, R_F.1, VDD_CORE.14 (AVIN)
unnamed: R_FB1_1.2, R_FB2_1.1, VDD_CORE.2 (FB)
unnamed: IC1.4 (O), IC3.1 (I0)
unnamed: IC2.4 (O), IC3.2 (I1)
PG_C2M: IC2.1 (I0), J1.D1
PG_CORE: IC1.2 (I1), R_PG.1, VDD_CORE.3 (PGOOD), VDD_IO.12 (EN)
PG_IO: IC2.2 (I1), R_PG1.1, VDD_IO.3 (PGOOD)
PG_M2C: IC1.1 (I0), J1.F1
PRSNT_M2C_L: J1.H2
PWR_EN: JP5.2, VDD_CORE.12 (EN)
SCL: J1.C30
SDA: J1.C31
TCK: J1.D29
TDI: J1.D30
TDO: J1.D31
TMS: J1.D33
TRST_L: J1.D34
VADJ: J1.E39, J1.F40, J1.G39, J1.H40
VDD_CORE: C_OUT.1, L_CORE.2, R_FB1_1.1, SV1.2, U$2.P$6 (VDD_CORE), U$2.P$58 (VDD_CORE)
VDD_IO: C_OUT1.1, L_IO.2, R_FB1_2.1, SV1.3, U$2.P$38 (VDD_IO), U$2.P$66 (VDD_IO)
VREF: J1.H1

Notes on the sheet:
Power
Connectors
FMC Connector
Core Voltage Regulator
*Voltage regulation for the core and IO. The core is not adjustable, it is fixed at 1.2V using a buck converter. The IO is also a fixed voltage but at 1.5V.
*BNC connectors for voltage, current or logic probes.
*5V input power from barrel connector. Supplementary power from FMC is not used to prevent burning out the carrier card.
*FMC board to board connector labeled with the pins from the Trenz Electronic TEBF0808 connector board.
IO Voltage Regulator
Power Verification
Logic to check all power good signals, once final signal is high then power has reached operating conditions. This logic is currently unused.
QFN80 footprint with layout for the ASS3145-QFN80-0.5-CL socket. There are two power supplies, one for the core voltage (1.2V) and one for IO (1.5V).
Power enable jumper to allow power cycling through IO. For board testing disconnect the jumper and connect PWR_EN to 5V source.

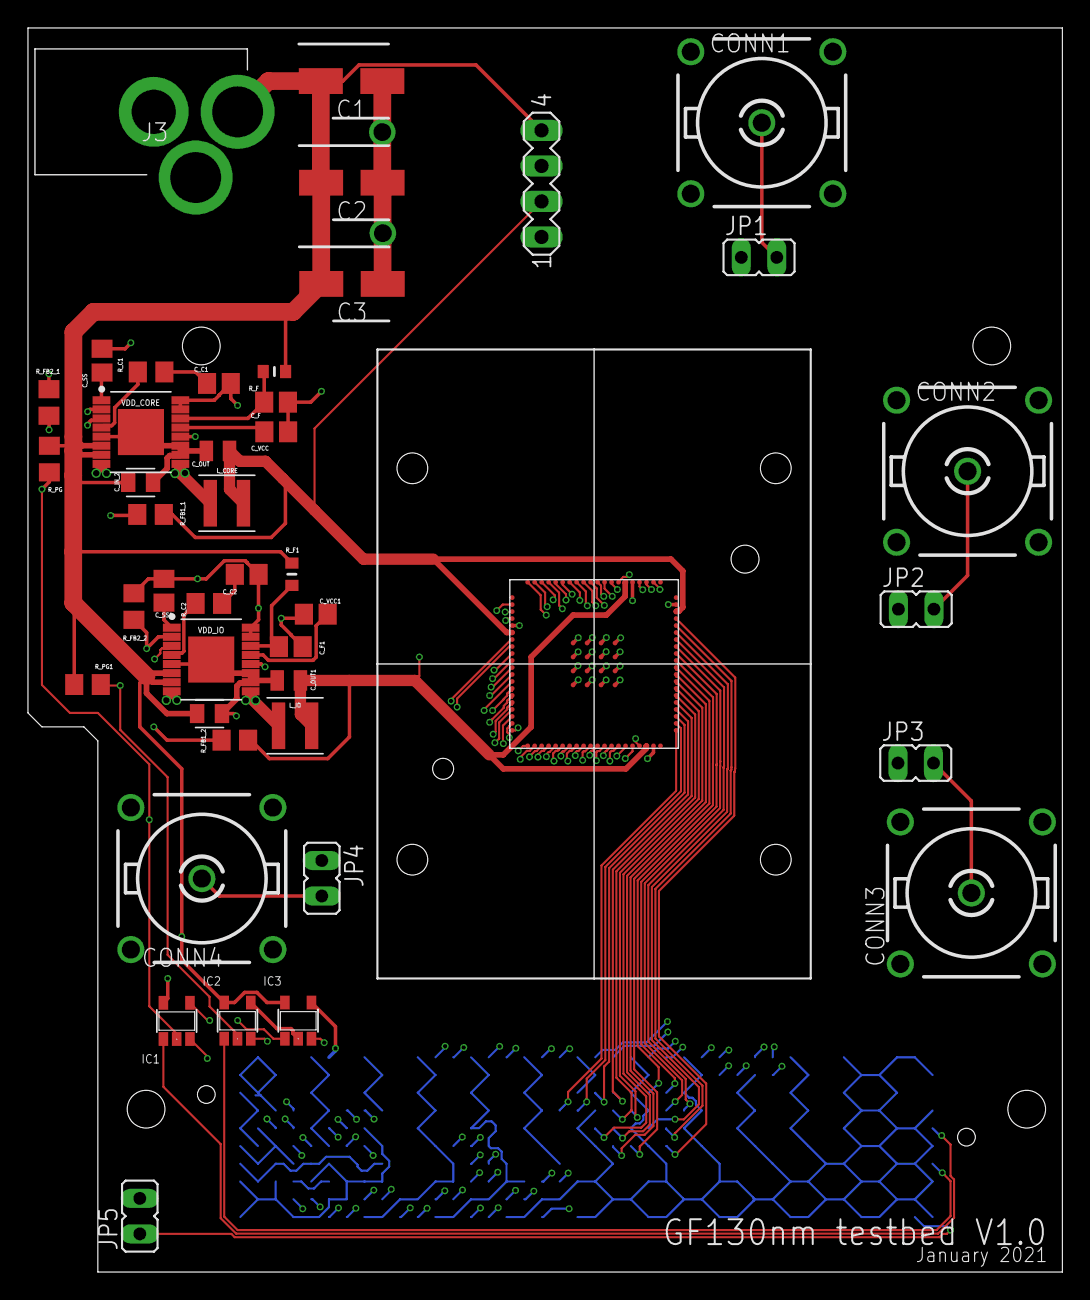
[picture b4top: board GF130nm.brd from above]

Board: 4 copper layers, 74.0 x 89.0 mm, 45 parts (1 on the bottom side), 102 nets.
